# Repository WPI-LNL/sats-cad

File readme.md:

# Small Asset Tracking System (SATS)

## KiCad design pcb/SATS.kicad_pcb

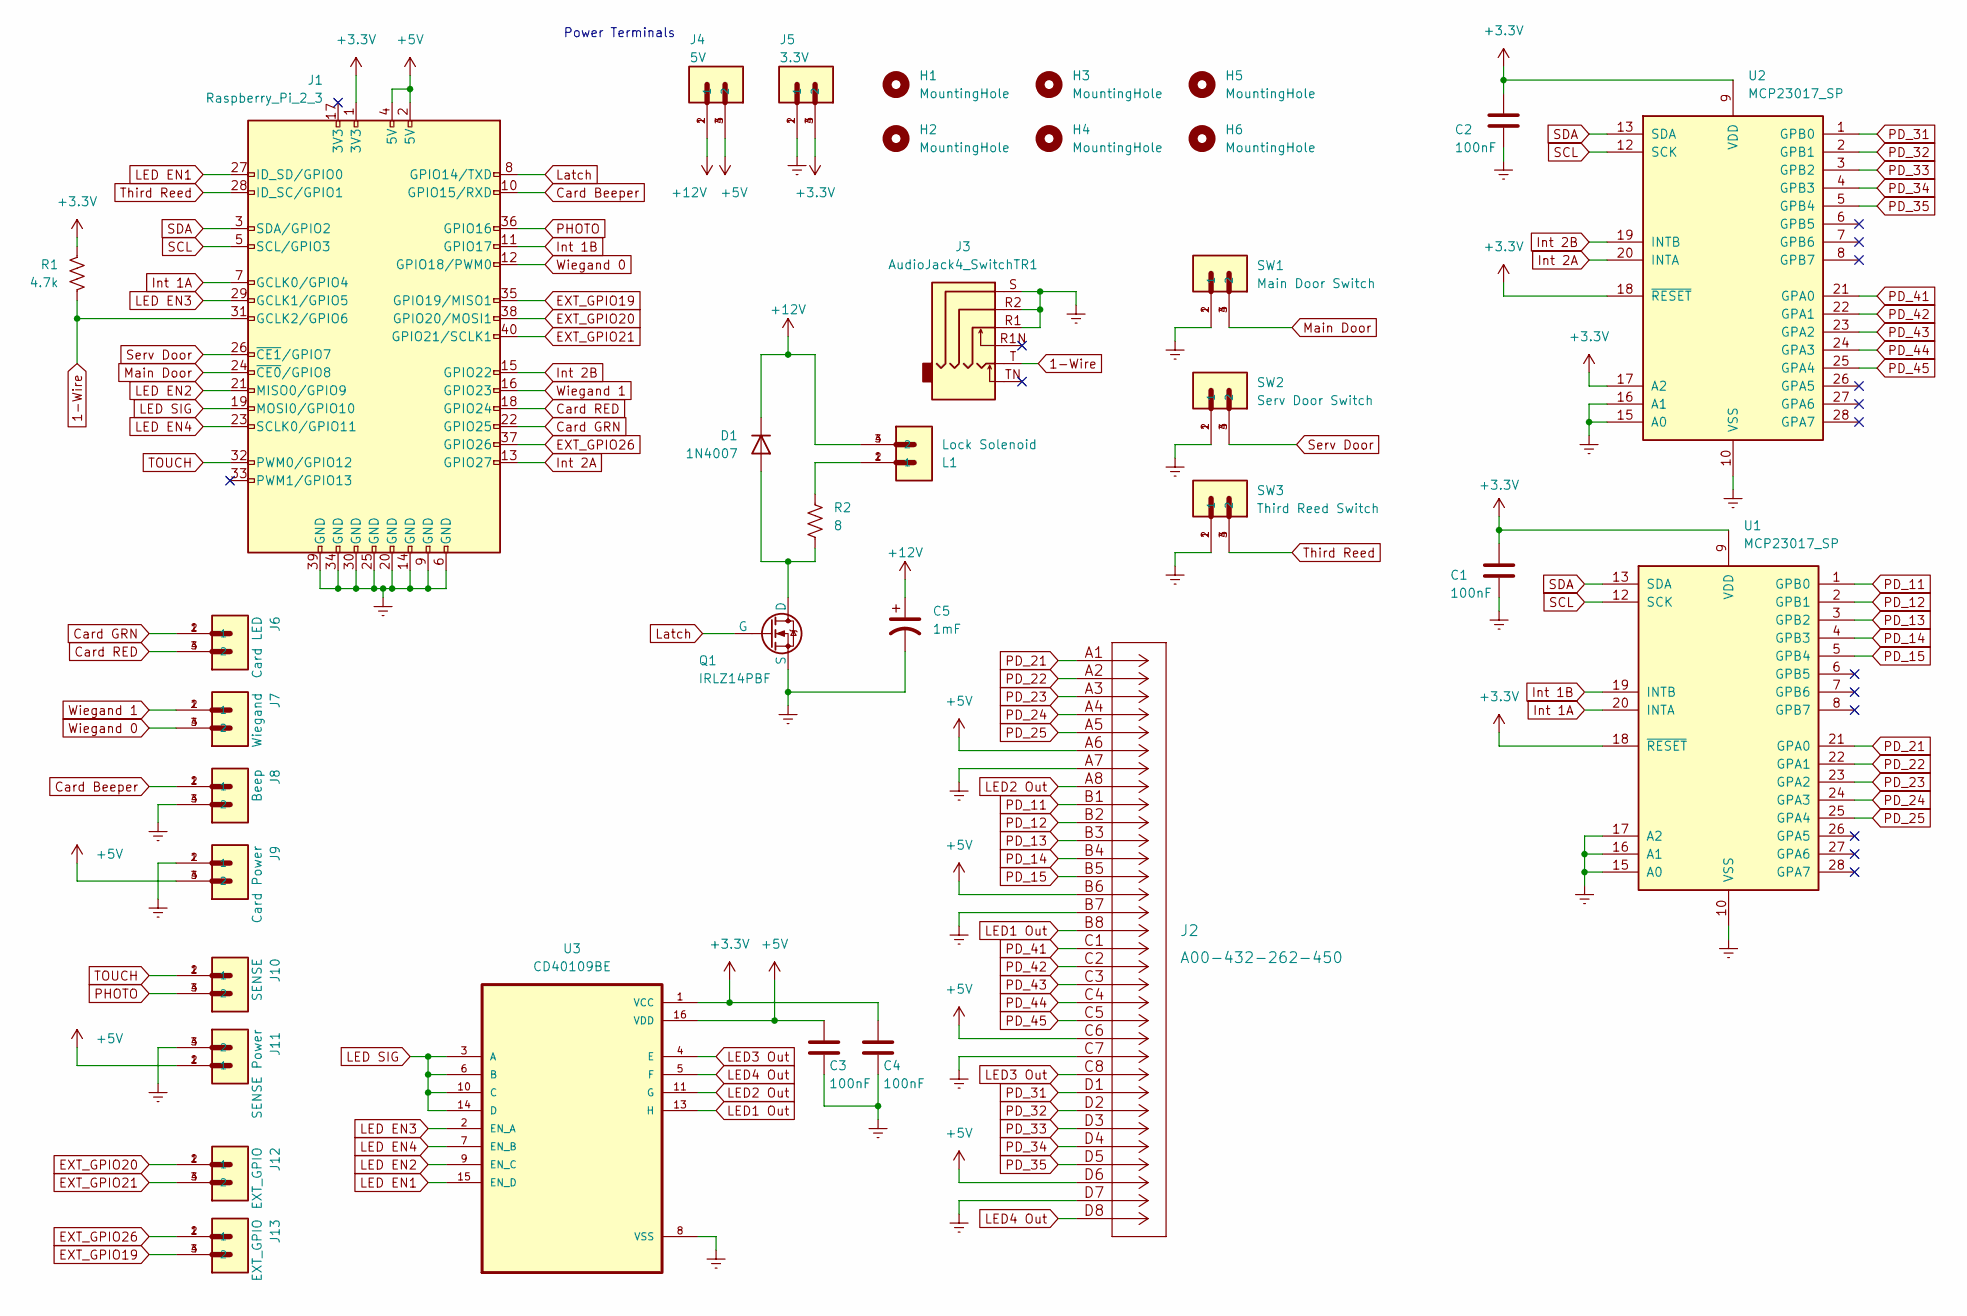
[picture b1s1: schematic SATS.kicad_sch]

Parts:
C1, C2, C3, C4: 100nF; C_Rect_L7.0mm_W3.5mm_P5.00mm
C5: 1mF; CP_Radial_D10.0mm_P5.00mm
D1: 1N4007; D_DO-41_SOD81_P10.16mm_Horizontal
H1, H2, H3, H4, H5, H6: MountingHole; MountingHole_2.7mm_M2.5
J1: Raspberry_Pi_2_3; PinSocket_2x20_P2.54mm_Vertical
J2: A00-432-262-450
J3: AudioJack4_SwitchTR1; AudioJack4_6pad
J4: 5V; PHOENIX_1862042; PARTREV 01/24/2018
J5: 3.3V; PHOENIX_1862042; PARTREV 01/24/2018
J6: Card LED; PHOENIX_1862042; PARTREV 01/24/2018
J7: Wiegand; PHOENIX_1862042; PARTREV 01/24/2018
J8: Beep; PHOENIX_1862042; PARTREV 01/24/2018
J9: Card Power; PHOENIX_1862042; PARTREV 01/24/2018
J10: SENSE; PHOENIX_1862042; PARTREV 01/24/2018
J11: SENSE Power; PHOENIX_1862042; PARTREV 01/24/2018
J12, J13: EXT_GPIO; PHOENIX_1862042; PARTREV 01/24/2018
L1: Lock Solenoid; PHOENIX_1862042; PARTREV 01/24/2018
Q1: IRLZ14PBF; TO-220-3_Horizontal_TabDown
R1: 4.7k; R_Axial_DIN0207_L6.3mm_D2.5mm_P7.62mm_Horizontal
R2: 8; R_Axial_DIN0207_L6.3mm_D2.5mm_P7.62mm_Horizontal
SW1: Main Door Switch; PHOENIX_1862042; PARTREV 01/24/2018
SW2: Serv Door Switch; PHOENIX_1862042; PARTREV 01/24/2018
SW3: Third Reed Switch; PHOENIX_1862042; PARTREV 01/24/2018
U1, U2: MCP23017_SP; DIP-28_W7.62mm
U3: CD40109BE; DIP-16_W7.62mm

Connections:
1-Wire: J1.31 (GCLK2/GPIO6), J3.T, R1.1
+3V3: C1.1, C2.1, C4.1, J1.1 (3V3), J5.3 (2), J5.4 (2), R1.2, U1.9 (VDD), U1.18 (~RESET), U2.9 (VDD), U2.17 (A2), U2.18 (~RESET), U3.1 (VCC)
+5V: C3.1, J1.2 (5V), J1.4 (5V), J2.A6, J2.B6, J2.C6, J2.D6, J4.3 (2), J4.4 (2), J9.3 (2), J9.4 (2), J11.1, J11.2 (1), U3.16 (VDD)
+12V: C5.1, D1.1 (K), J4.1, J4.2 (1), L1.3 (2), L1.4 (2)
Card Beeper: J1.10 (GPIO15/RXD), J8.1, J8.2 (1)
Card GRN: J1.22 (GPIO25), J6.1, J6.2 (1)
Card RED: J1.18 (GPIO24), J6.3 (2), J6.4 (2)
EXT_GPIO19: J1.35 (GPIO19/MISO1), J13.3 (2), J13.4 (2)
EXT_GPIO20: J1.38 (GPIO20/MOSI1), J12.1, J12.2 (1)
EXT_GPIO21: J1.40 (GPIO21/SCLK1), J12.3 (2), J12.4 (2)
EXT_GPIO26: J1.37 (GPIO26), J13.1, J13.2 (1)
Earth: C1.2, C2.2, C3.2, C4.2, C5.2, J1.6 (GND), J1.9 (GND), J1.14 (GND), J1.20 (GND), J1.25 (GND), J1.30 (GND), J1.34 (GND), J1.39 (GND), J2.A7, J2.B7, J2.C7, J2.D7, J3.R1, J3.R2, J3.S, J5.1, J5.2 (1), J8.3 (2), J8.4 (2), J9.1, J9.2 (1), J11.3 (2), J11.4 (2), Q1.3 (S), SW1.1, SW1.2 (1), SW2.1, SW2.2 (1), SW3.1, SW3.2 (1), U1.10 (VSS), U1.15 (A0), U1.16 (A1), U1.17 (A2), U2.10 (VSS), U2.15 (A0), U2.16 (A1), U3.8 (VSS)
Int 1A: J1.7 (GCLK0/GPIO4), U1.20 (INTA)
Int 1B: J1.11 (GPIO17), U1.19 (INTB)
Int 2A: J1.13 (GPIO27), U2.20 (INTA)
Int 2B: J1.15 (GPIO22), U2.19 (INTB)
LED1 Out: J2.B8, U3.13 (H)
LED2 Out: J2.A8, U3.11 (G)
LED3 Out: J2.C8, U3.4 (E)
LED4 Out: J2.D8, U3.5 (F)
LED EN1: J1.27 (ID_SD/GPIO0), U3.15 (EN_D)
LED EN2: J1.21 (MISO0/GPIO9), U3.9 (EN_C)
LED EN3: J1.29 (GCLK1/GPIO5), U3.2 (EN_A)
LED EN4: J1.23 (SCLK0/GPIO11), U3.7 (EN_B)
LED SIG: J1.19 (MOSI0/GPIO10), U3.3 (A), U3.6 (B), U3.10 (C), U3.14 (D)
Latch: J1.8 (GPIO14/TXD), Q1.1 (G)
Main Door: J1.24 (~CE0/GPIO8), SW1.3 (2), SW1.4 (2)
unnamed: D1.2 (A), Q1.2 (D), R2.2
unnamed: L1.1, L1.2 (1), R2.1
PD_11: J2.B1, U1.1 (GPB0)
PD_12: J2.B2, U1.2 (GPB1)
PD_13: J2.B3, U1.3 (GPB2)
PD_14: J2.B4, U1.4 (GPB3)
PD_15: J2.B5, U1.5 (GPB4)
PD_21: J2.A1, U1.21 (GPA0)
PD_22: J2.A2, U1.22 (GPA1)
PD_23: J2.A3, U1.23 (GPA2)
PD_24: J2.A4, U1.24 (GPA3)
PD_25: J2.A5, U1.25 (GPA4)
PD_31: J2.D1, U2.1 (GPB0)
PD_32: J2.D2, U2.2 (GPB1)
PD_33: J2.D3, U2.3 (GPB2)
PD_34: J2.D4, U2.4 (GPB3)
PD_35: J2.D5, U2.5 (GPB4)
PD_41: J2.C1, U2.21 (GPA0)
PD_42: J2.C2, U2.22 (GPA1)
PD_43: J2.C3, U2.23 (GPA2)
PD_44: J2.C4, U2.24 (GPA3)
PD_45: J2.C5, U2.25 (GPA4)
PHOTO: J1.36 (GPIO16), J10.3 (2), J10.4 (2)
SCL: J1.5 (SCL/GPIO3), U1.12 (SCK), U2.12 (SCK)
SDA: J1.3 (SDA/GPIO2), U1.13 (SDA), U2.13 (SDA)
Serv Door: J1.26 (~CE1/GPIO7), SW2.3 (2), SW2.4 (2)
TOUCH: J1.32 (PWM0/GPIO12), J10.1, J10.2 (1)
Third Reed: J1.28 (ID_SC/GPIO1), SW3.3 (2), SW3.4 (2)
Wiegand 0: J1.12 (GPIO18/PWM0), J7.3 (2), J7.4 (2)
Wiegand 1: J1.16 (GPIO23), J7.1, J7.2 (1)

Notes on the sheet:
Power Terminals

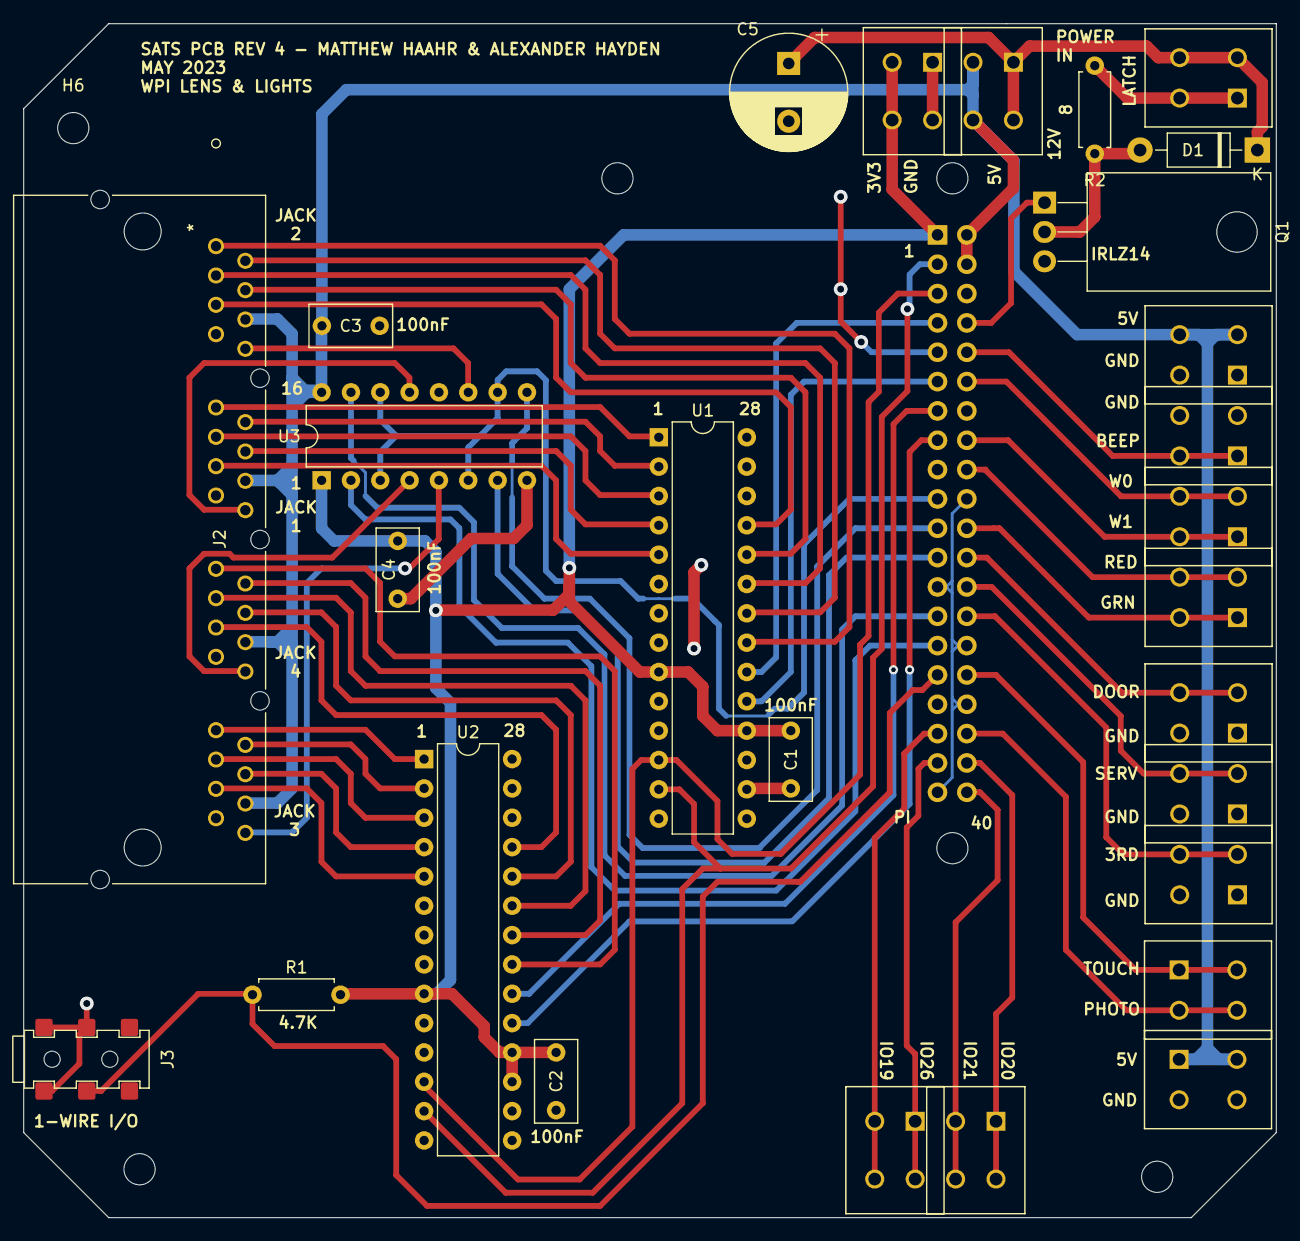
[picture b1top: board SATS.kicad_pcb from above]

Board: 2 copper layers, 108.5 x 103.4 mm, 35 parts (1 on the bottom side), 57 nets.

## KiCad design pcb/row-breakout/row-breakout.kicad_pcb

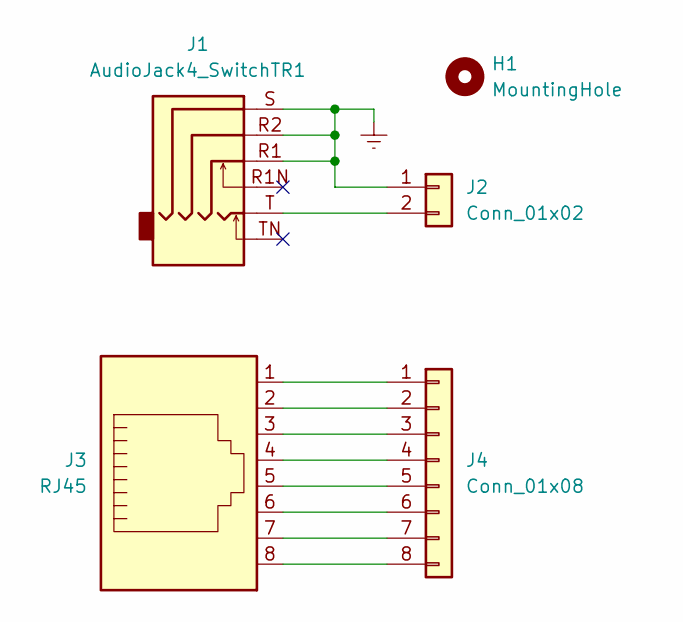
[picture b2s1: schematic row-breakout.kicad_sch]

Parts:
H1: MountingHole; MountingHole_2.7mm_M2.5
J1: AudioJack4_SwitchTR1; AudioJack4_6pad
J2: Conn_01x02; PinSocket_1x02_P2.54mm_Vertical
J3: RJ45; RJ45_Amphenol_54602-x08_Horizontal
J4: Conn_01x08; PinSocket_1x08_P2.54mm_Vertical

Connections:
Earth: J1.R1, J1.R2, J1.S, J2.1
unnamed: J1.T, J2.2
unnamed: J3.1, J4.1
unnamed: J3.2, J4.2
unnamed: J3.3, J4.3
unnamed: J3.4, J4.4
unnamed: J3.5, J4.5
unnamed: J3.6, J4.6
unnamed: J3.7, J4.7
unnamed: J3.8, J4.8

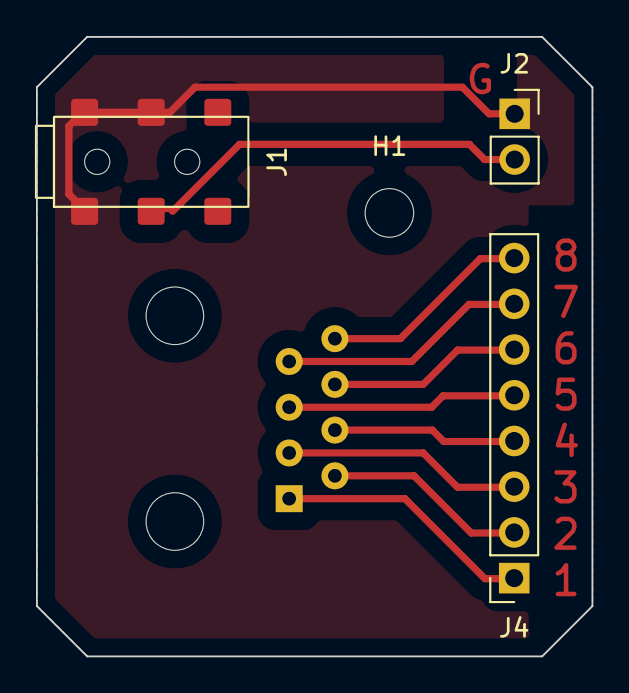
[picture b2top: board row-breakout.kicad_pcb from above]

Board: 2 copper layers, 30.9 x 34.4 mm, 5 parts (1 on the bottom side), 10 nets.

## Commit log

2022-04-28 init
2022-04-28 initial kicad
2023-03-18 Start Electrical Design
2023-03-18 Starting Parts Collection
2023-03-18 Add Solenoid circuit
2023-03-19 Start Net building
2023-03-19 remove unneeded pullups, add level shifter ins
2023-03-19 actually move 1-wire
2023-03-19 Route jacks
2023-03-19 add audio jack footprint
2023-03-19 Add Alignment throughholesor jack
2023-03-21 Create, circuit, and route Breakouts
2023-03-21 Add terminal connectors for solenoid and switches
2023-03-21 Add Power Connectors
2023-03-23 Add Card LED Terminals
2023-03-23 Finish Schematic
2023-03-24 Flip RJ45 on Row Breakout for Single Side Board
2023-03-24 neatify and reorganize
2023-03-24 Route PD lines
2023-03-24 Clead PD Lines and route LED Outs
2023-03-26 mostly done
2023-03-26 Clean Board Edge and Foottprints
2023-03-26 add copper labels
2023-03-26 Add Mounting Holes and Fix Errors
2023-03-28 Generate Step File
2023-03-28 Add breakout steps
2023-03-28 Create Gerbers
2023-04-11 Added <no-net> Copper Fills
2023-04-11 Add Grounded Copper Fills to Row Breakout and Main Board
2023-04-11 Add power cap for Latch
2023-04-18 Update for better gerbers
2023-05-02 Rev 3 Complete
2023-05-02 Fix resistor, redate
2023-05-02 Reev 3
2023-05-05 Rev 4 - Pretest
2023-05-05 Fix MOSFET
